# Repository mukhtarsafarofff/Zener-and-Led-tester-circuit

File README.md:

(ENG)  With This small circuit we can test Led and Zener diodes, so we can sure that Led or Zener diode is not working or just working .
(DEU)  Mithilfe dieser kleinen Schaltung können wir LED- und Zener-Dioden testen und so sicher sein, dass LED oder Zener-Diode nicht oder nur funktionieren .

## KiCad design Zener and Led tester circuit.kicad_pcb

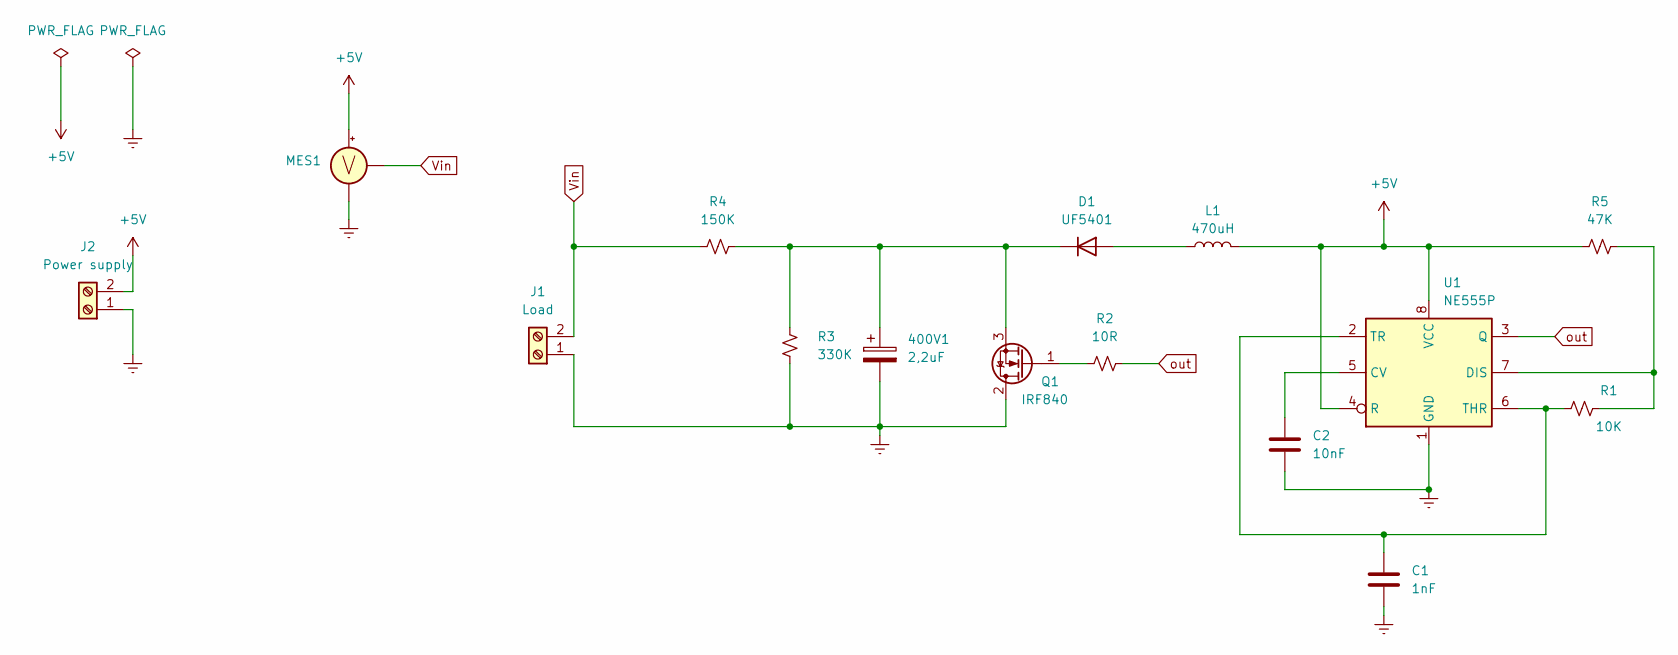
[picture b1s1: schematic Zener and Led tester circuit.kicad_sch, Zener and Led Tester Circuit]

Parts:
400V1: 2,2uF; CP_Radial_D13.0mm_P7.50mm
C1: 1nF; C_Disc_D7.5mm_W5.0mm_P7.50mm
C2: 10nF; C_Disc_D7.5mm_W5.0mm_P10.00mm
D1: UF5401; D_DO-201AD_P15.24mm_Horizontal
J1: Load; TerminalBlock_bornier-2_P5.08mm
J2: Power supply; TerminalBlock_bornier-2_P5.08mm
L1: 470uH; L_Axial_L9.5mm_D4.0mm_P15.24mm_Horizontal_Fastron_SMCC
MES1: VOLTMETER_DIFF
Q1: IRF840; TO-220-3_Vertical
R1: 10K; R_Axial_DIN0411_L9.9mm_D3.6mm_P12.70mm_Horizontal
R2: 10R; R_Axial_DIN0411_L9.9mm_D3.6mm_P12.70mm_Horizontal
R3: 330K; R_Axial_DIN0411_L9.9mm_D3.6mm_P12.70mm_Horizontal
R4: 150K; R_Axial_DIN0411_L9.9mm_D3.6mm_P12.70mm_Horizontal
R5: 47K; R_Axial_DIN0411_L9.9mm_D3.6mm_P12.70mm_Horizontal
U1: NE555P; DIP-8_W7.62mm

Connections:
+5V: J2.2, L1.2, MES1.1 (+), R5.1, U1.4 (R), U1.8 (VCC)
Earth: 400V1.2, C1.1, C2.2, J1.1, J2.1, MES1.2 (-), Q1.2 (D), R3.2, U1.1 (GND)
unnamed: D1.2 (A), L1.1
unnamed: 400V1.1, D1.1 (K), Q1.3 (S), R3.1, R4.2
unnamed: Q1.1 (G), R2.1
unnamed: C2.1, U1.5 (CV)
unnamed: R1.2, R5.2, U1.7 (DIS)
unnamed: C1.2, R1.1, U1.2 (TR), U1.6 (THR)
Vin: J1.2, MES1.3 (out), R4.1
out: R2.2, U1.3 (Q)

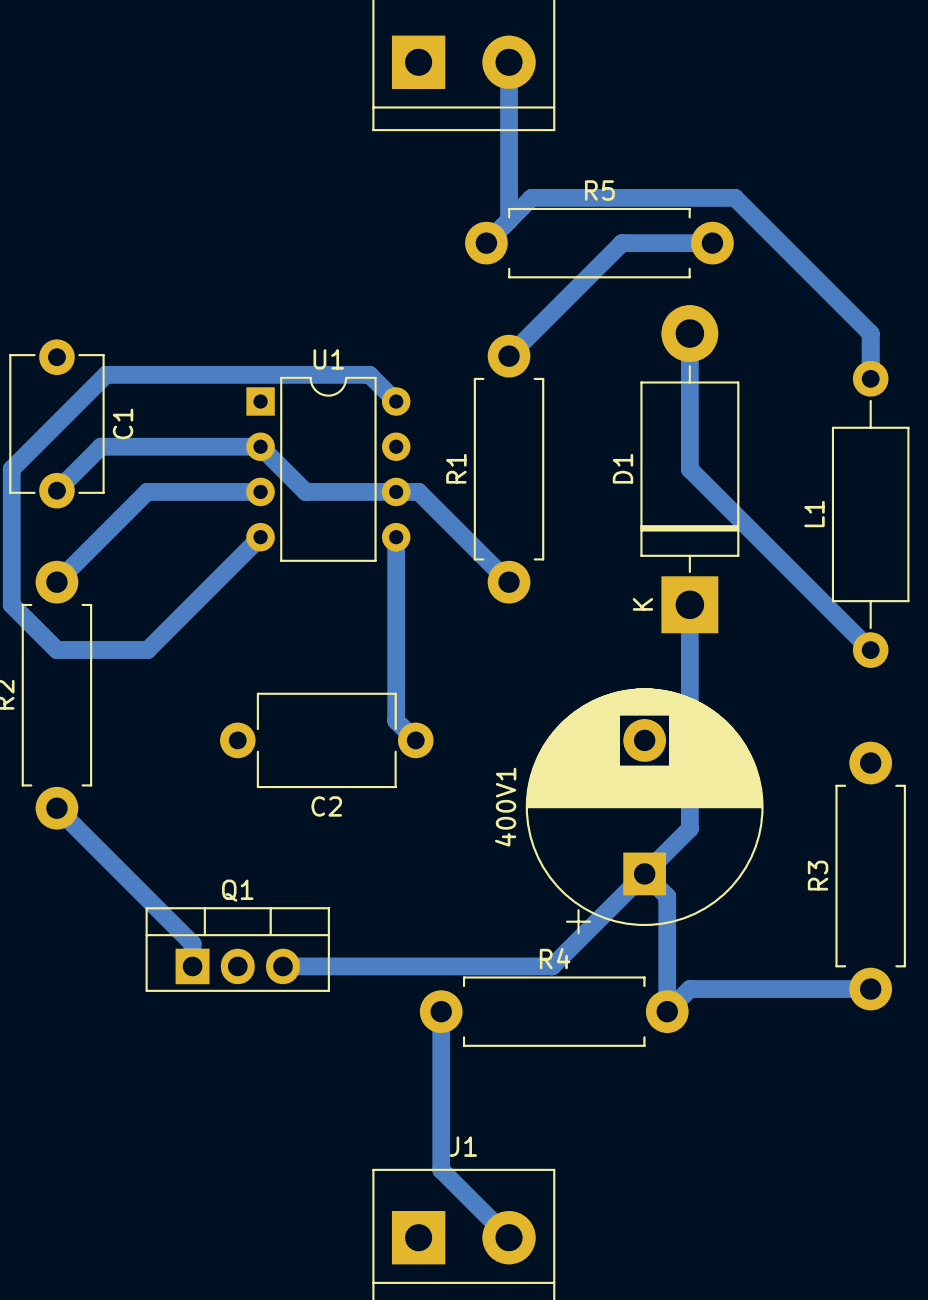
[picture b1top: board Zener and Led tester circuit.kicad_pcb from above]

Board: 2 copper layers, 14 parts (0 on the bottom side), 10 nets.

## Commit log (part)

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2024-03-17 Zener Diod and LED Tester Circuit is completed
2024-03-26 Zener and Led Tester Circuit is renewed
